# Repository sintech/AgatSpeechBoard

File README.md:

# Agat Speech Board

КР1803ВЖ1 (TMS5100) based speech synthesizer board for [Agat](https://en.wikipedia.org/wiki/Agat_(computer)) computer.

Schematics was designed in KiCad EDA with a custom parts lib.
Software was created using [cc65](https://cc65.github.io/) compiler. And it works on Agat only in Apple II compatibility mode.

## Project files
- Schematics in KiCad format: [schematics/AgatSpeechBoard](schematics/AgatSpeechBoard), PNG: [Control](schematics/AgatSpeechBoard/AgatSpeechBoard_sch.png), [Analog](schematics/AgatSpeechBoard/AgatSpeechBoard_analog_sch.png)
- ATF16v8 PLD firmware: [PLD Firmware](src/ATF16V8)
- Speak program sources for Agat-9 Apple II mode: [src/speak](src/speak)
- Various datasheets for КР1803ВЖ1 and TMS5100 chips: [docs](docs)
- "Talking Dice" circuit based on TMS5100 chip: [docs/Talking Dice](docs/Talking%20Dice)

## [Chaos Constructions 2019](http://c-c.ru) public report
- Presentation (in Russian): [Синтезатор речи для ПЭВМ Агат.pdf](docs/Синтезатор%20речи%20для%20ПЭВМ%20Агат.pdf)
- Full software demo: https://www.youtube.com/watch?v=xI7s3mxBhng
- Russian phrases: https://www.youtube.com/watch?v=0sAlXTVFXQc
- Speak and Spell emulator: https://www.youtube.com/watch?v=E4hqrfArUSM

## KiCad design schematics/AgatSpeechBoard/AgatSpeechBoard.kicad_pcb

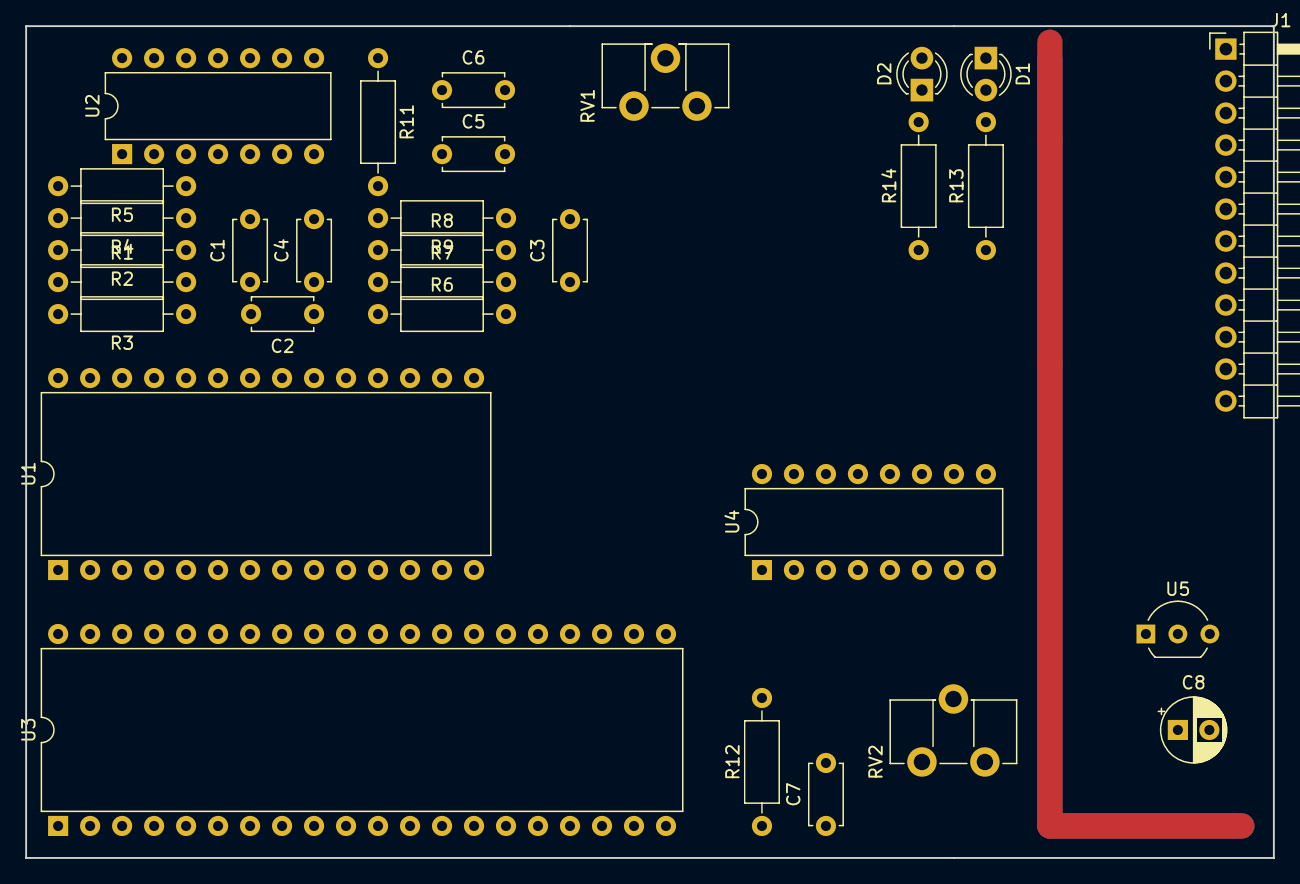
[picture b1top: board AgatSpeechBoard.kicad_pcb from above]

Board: 2 copper layers, 99.1 x 66.0 mm, 31 parts (0 on the bottom side), 29 nets.

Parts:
C1, C2, C5: 1n; C_Disc_D4.7mm_W2.5mm_P5.00mm
C3, C4: 10n; C_Disc_D4.7mm_W2.5mm_P5.00mm
C6: 100n; C_Disc_D4.7mm_W2.5mm_P5.00mm
C7: 68p; C_Disc_D4.7mm_W2.5mm_P5.00mm
C8: 10uF 25v; CP_Radial_D5.0mm_P2.50mm
D1: Red; LED_D3.0mm
D2: Yellow; LED_D3.0mm
J1: Conn_01x12_Female; PinHeader_1x12_P2.54mm_Horizontal
R1, R2: 47; R_Axial_DIN0207_L6.3mm_D2.5mm_P10.16mm_Horizontal
R3, R4, R5, R6, R8, R12: 10k; R_Axial_DIN0207_L6.3mm_D2.5mm_P10.16mm_Horizontal
R7: 12k; R_Axial_DIN0207_L6.3mm_D2.5mm_P10.16mm_Horizontal
R9: 6k8; R_Axial_DIN0207_L6.3mm_D2.5mm_P10.16mm_Horizontal
R11: 20k; R_Axial_DIN0207_L6.3mm_D2.5mm_P10.16mm_Horizontal
R13, R14: 500; R_Axial_DIN0207_L6.3mm_D2.5mm_P10.16mm_Horizontal
RV1: 22k; Potentiometer_ACP_CA9-H3,8_Horizontal
RV2: 50k; Potentiometer_ACP_CA9-H5_Horizontal
U1: TMS5100NL; DIP-28_W15.24mm
U2: TL084; DIP-14_W7.62mm
U3: KR1803VZH1; DIP-40_W15.24mm
U4: 4050; DIP-16_W7.62mm
U5: L7905; TO-92_Inline_Wide

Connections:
+5V: J1.4, R13.1, U1.14, U2.4, U3.18, U3.40, U4.1
-5V: C7.1, C8.2, R1.2, R2.1, R12.1, R14.1, U1.5, U2.11, U3.5, U3.13, U5.3
/-12v: J1.12, U5.2
/ADDR8: J1.3, U4.3
/Audio_OUT: J1.10, RV1.2
/CTRL1: J1.8, U1.25, U3.36
/CTRL2+8: J1.5, U4.5
/CTRL4: J1.6, U4.7
/IO_M0: J1.2, U1.15, U3.22
/PDC: J1.7, U4.9
/SPK1: R1.1, R3.2, U1.11, U3.15
/SPK2: R2.2, R4.2, U1.12, U3.16
GND: C1.2, C3.2, C4.2, C8.1, D1.1, D2.2, J1.1, R5.2, RV1.3, U2.5, U4.8, U5.1
unnamed: C1.1, R4.1, R5.1, U2.3
unnamed: C2.1, R6.1, R7.1, U2.1
unnamed: C2.2, R3.1, R6.2, U2.2
unnamed: C3.1, R7.2, R8.2
unnamed: C4.1, R8.1, R9.2, R11.2
unnamed: C5.1, C6.1, R11.1, U2.7
unnamed: C5.2, R9.1, U2.6
unnamed: C6.2, RV1.1
unnamed: C7.2, RV2.2, RV2.3, U1.7, U3.11
unnamed: D1.2, R13.2
unnamed: D2.1, R14.2
unnamed: R12.2, RV2.1
unnamed: U1.2, U3.2, U4.10
unnamed: U1.20, U3.28, U4.6
unnamed: U1.23, U1.27, U3.33, U3.38, U4.4
unnamed: U1.26, U3.37, U4.2

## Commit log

2019-09-04 initial
